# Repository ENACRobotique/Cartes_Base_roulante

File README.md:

# Carte_Base_roulante_2024
Carte custom pour une base roulante holonome basé sur la STM32G484Retx
Conçue pour d'elle même faire de l'odométrie par encodeur et gyroscope.
Le debug nécéssite une sonde externe.

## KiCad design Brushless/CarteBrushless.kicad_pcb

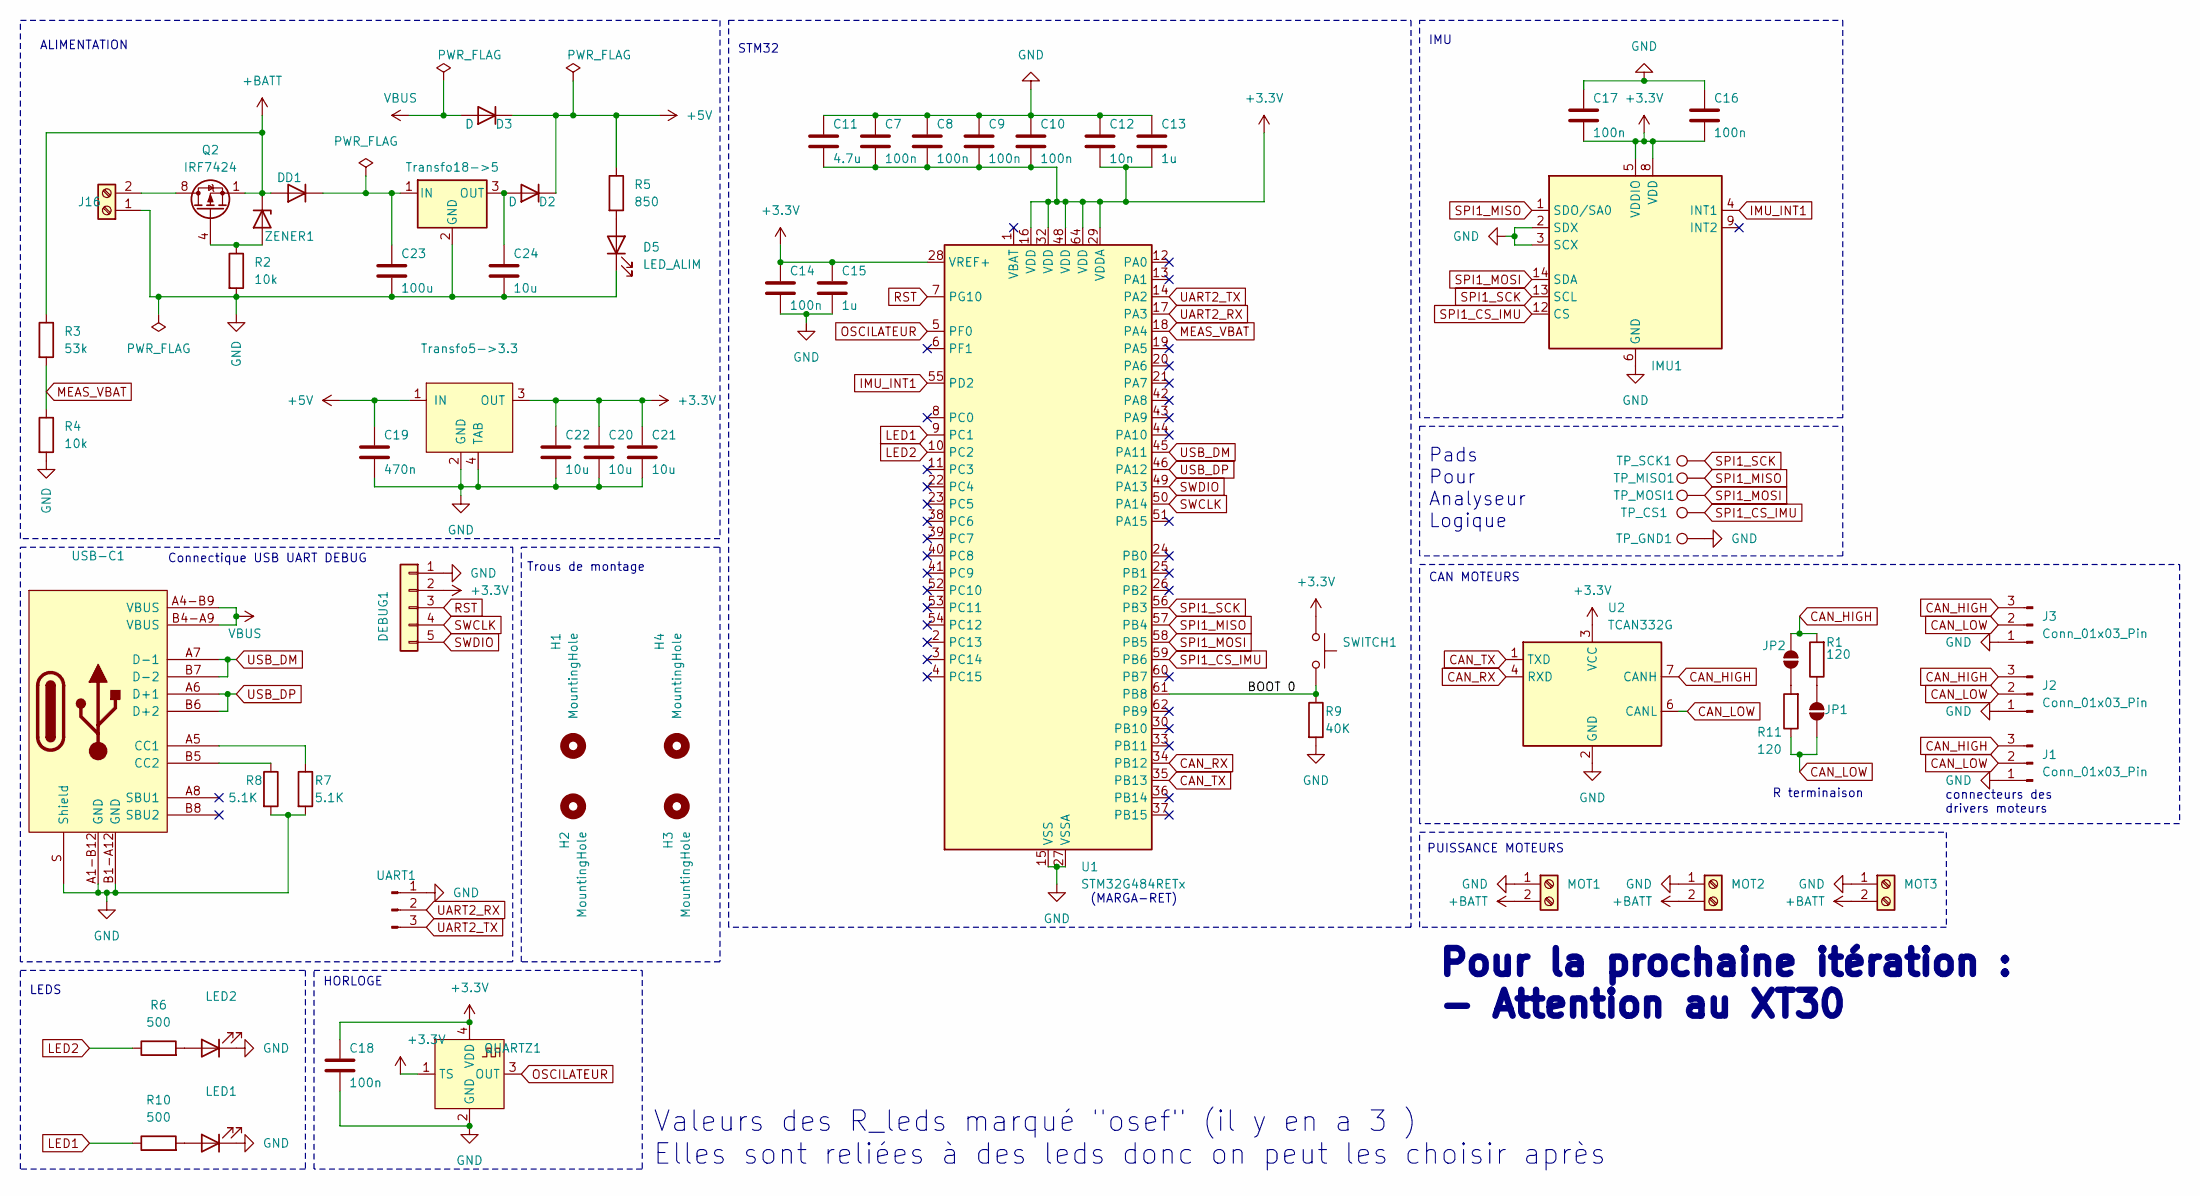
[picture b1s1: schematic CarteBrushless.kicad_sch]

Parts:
C7, C8, C9, C10, C14, C16, C17, C18: 100n; C_0603_1608Metric
C11: 4.7u; C_0603_1608Metric
C12: 10n; C_0603_1608Metric
C13, C15: 1u; C_0603_1608Metric
C19: 470n; C_0603_1608Metric
C20, C21, C22, C24: 10u; C_0603_1608Metric
C23: 100u; CP_EIA-7343-31_Kemet-D_Pad2.25x2.55mm_HandSolder
D1, D2, D3: D; Nexperia_CFP3_SOD-123W
D5: LED_ALIM; LED_0603_1608Metric
DEBUG1: DEBUG; Molex_PicoBlade_53398-0571_1x05-1MP_P1.25mm_Vertical
H1, H2, H3, H4: MountingHole; MountingHole_3.2mm_M3
IMU1: LSM6DSL; LGA-14_3x2.5mm_P0.5mm_LayoutBorder3x4y
J1, J2, J3: Conn_01x03_Pin; Molex_PicoBlade_53398-0371_1x03-1MP_P1.25mm_Vertical
J16: ALIM; TerminalBlock_bornier-2_P5.08mm
JP1, JP2: SolderJumper_2_Open; SolderJumper-2_P1.3mm_Open_RoundedPad1.0x1.5mm
LED1: LED1; LED_0603_1608Metric_Pad1.05x0.95mm_HandSolder
LED2: LED2; LED_0603_1608Metric_Pad1.05x0.95mm_HandSolder
MOT1, MOT2, MOT3: MOT3; AMASS_XT30UPB-F_1x02_P5.0mm_Vertical
Q2: IRF7424; SOIC-8_3.9x4.9mm_P1.27mm
QUARTZ1: ASCO; Osc_ASCO
R1, R11: 120; R_0805_2012Metric
R2, R4: 10k; R_0805_2012Metric
R3: 53k; R_0805_2012Metric
R5: 850; R_0805_2012Metric
R6, R10: 500; R_0805_2012Metric
R7, R8: 5.1K; R_0603_1608Metric
R9: 40K; R_0805_2012Metric
SWITCH1: SW_Push; SWITCH_DTSM31NV
TP_CS1: TestPoint; TestPoint_Pad_D1.5mm
TP_GND1: TestPoint; TestPoint_Pad_D1.5mm
TP_MISO1: TestPoint; TestPoint_Pad_D1.5mm
TP_MOSI1: TestPoint; TestPoint_Pad_D1.5mm
TP_SCK1: TestPoint; TestPoint_Pad_D1.5mm
Transfo5->3.3: LM3940IMP-3.3; LM3940IMP
Transfo18->5: R-78E5.0-1.0; Converter_DCDC_RECOM_R-78E-0.5_THT
U1: STM32G484RETx; LQFP-64_10x10mm_P0.5mm
U2: TCAN332G; SOT-23-8
UART1: Conn_01x03_Pin; Molex_PicoBlade_53398-0371_1x03-1MP_P1.25mm_Vertical
USB-C1: USB-C_12pin; USB-C_HRO_C-31-M-12
ZENER1: D_Zener; D_SOD-523

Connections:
+3.3V: C7.2, C8.2, C9.2, C10.2, C11.2, C12.2, C13.2, C14.1, C15.1, C16.2, C17.2, C18.1, C20.1, C21.1, C22.1, DEBUG1.2, IMU1.5 (VDDIO), IMU1.8 (VDD), QUARTZ1.1 (TS), QUARTZ1.4 (VDD), SWITCH1.1, Transfo5->3.3.3 (OUT), U1.16 (VDD), U1.28 (VREF+), U1.29 (VDDA), U1.32 (VDD), U1.48 (VDD), U1.64 (VDD), U2.3 (VCC)
+5V: C19.1, D2.1 (K), D3.1 (K), R5.1, Transfo5->3.3.1 (IN)
+BATT: D1.2 (A), MOT1.2, MOT2.2, MOT3.2, Q2.1 (S), Q2.2 (S), Q2.3 (S), R3.1, ZENER1.1 (K)
/BOOT 0: R9.1, SWITCH1.2, U1.61 (PB8)
CAN_HIGH: J1.3, J2.3, J3.3, JP2.2 (B), R1.2, U2.7 (CANH)
CAN_LOW: J1.2, J2.2, J3.2, JP1.1 (A), R11.1, U2.6 (CANL)
CAN_RX: U1.34 (PB12), U2.4 (RXD)
CAN_TX: U1.35 (PB13), U2.1 (TXD)
GND: C7.1, C8.1, C9.1, C10.1, C11.1, C12.1, C13.1, C14.2, C15.2, C16.1, C17.1, C18.2, C19.2, C20.2, C21.2, C22.2, C23.2, C24.2, D5.1 (K), DEBUG1.1, IMU1.2 (SDX), IMU1.3 (SCX), IMU1.6 (GND), IMU1.7 (GND), J1.1, J2.1, J3.1, LED1.1 (K), LED2.1 (K), MOT1.1, MOT2.1, MOT3.1, QUARTZ1.2 (GND), R2.2, R4.2, R7.2, R8.2, R9.2, TP_GND1.1, Transfo5->3.3.2 (GND), Transfo5->3.3.4 (TAB), Transfo18->5.2 (GND), U1.15 (VSS), U1.27 (VSSA), U1.31 (VSS), U1.47 (VSS), U1.63 (VSS), U2.2 (GND), UART1.1, USB-C1.A1-B12 (GND), USB-C1.B1-A12 (GND), USB-C1.S (Shield); also elsewhere on the board
IMU_INT1: IMU1.4 (INT1), U1.55 (PD2)
LED1: R10.1, U1.9 (PC1)
LED2: R6.1, U1.10 (PC2)
MEAS_VBAT: R3.2, R4.1, U1.18 (PA4)
unnamed 13: Q2.5 (D), Q2.6 (D), Q2.7 (D), Q2.8 (D); also elsewhere on the board
unnamed: C23.1, D1.1 (K), Transfo18->5.1 (IN)
unnamed: C24.1, D2.2 (A), Transfo18->5.3 (OUT)
unnamed: D5.2 (A), R5.2
unnamed: JP1.2 (B), R1.1
unnamed: JP2.1 (A), R11.2
unnamed: LED1.2 (A), R10.2
unnamed: LED2.2 (A), R6.2
unnamed: Q2.4 (G), R2.1, ZENER1.2 (A)
unnamed: R7.1, USB-C1.A5 (CC1)
unnamed: R8.1, USB-C1.B5 (CC2)
OSCILATEUR: QUARTZ1.3 (OUT), U1.5 (PF0)
RST: DEBUG1.3, U1.7 (PG10)
SPI1_CS_IMU: IMU1.12 (CS), TP_CS1.1, U1.59 (PB6)
SPI1_MISO: IMU1.1 (SDO/SA0), TP_MISO1.1, U1.57 (PB4)
SPI1_MOSI: IMU1.14 (SDA), TP_MOSI1.1, U1.58 (PB5)
SPI1_SCK: IMU1.13 (SCL), TP_SCK1.1, U1.56 (PB3)
SWCLK: DEBUG1.4, U1.50 (PA14)
SWDIO: DEBUG1.5, U1.49 (PA13)
UART2_RX: U1.17 (PA3), UART1.2
UART2_TX: U1.14 (PA2), UART1.3
USB_DM: U1.45 (PA11), USB-C1.A7 (D-1), USB-C1.B7 (D-2)
USB_DP: U1.46 (PA12), USB-C1.A6 (D+1), USB-C1.B6 (D+2)
VBUS: D3.2 (A), USB-C1.A4-B9 (VBUS), USB-C1.B4-A9 (VBUS)

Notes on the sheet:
Valeurs des R_leds marqué "osef" (il y en a 3 ) Elles sont reliées à des leds donc on peut les choisir après
IMU
LEDS
Trous de montage
connecteurs des drivers moteurs
CAN MOTEURS
HORLOGE
Pour la prochaine itération : - Attention au XT30
(MARGA-RET)
Pads Pour Analyseur Logique
PUISSANCE MOTEURS
STM32
ALIMENTATION
R terminaison
Connectique USB UART DEBUG

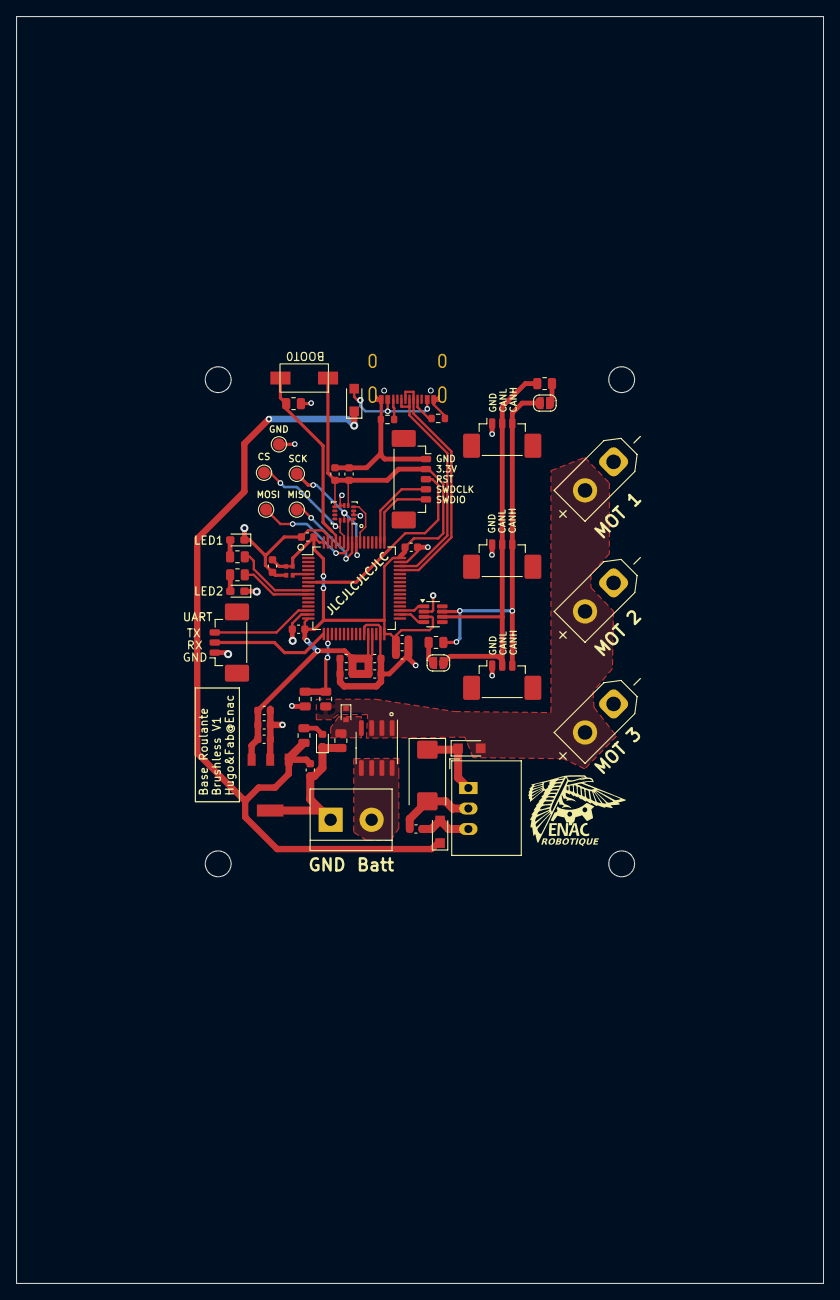
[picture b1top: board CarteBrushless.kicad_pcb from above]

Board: 2 copper layers, 100.0 x 157.0 mm, 65 parts (0 on the bottom side), 37 nets.

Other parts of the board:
ALIM1: ALIM; TerminalBlock_bornier-2_P5.08mm

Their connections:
GND: ALIM1.1; also elsewhere on the board
unnamed 13: ALIM1.2; also elsewhere on the board

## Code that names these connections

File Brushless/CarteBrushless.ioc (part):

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Mcu.Name=STM32G484RETx
Mcu.Package=LQFP64
Mcu.UserName=STM32G484RETx
PA11.Mode=Device
PA11.Signal=USB_DM
PA12.Mode=Device
PA12.Signal=USB_DP
PA13.Mode=Serial_Wire
PA13.Signal=SYS_JTMS-SWDIO
PA14.Mode=Serial_Wire
PA14.Signal=SYS_JTCK-SWCLK
PA2.Mode=Asynchronous
PA2.Signal=USART2_TX
PA3.Mode=Asynchronous
PA3.Signal=USART2_RX
PA4.Mode=IN17-Single-Ended
PA4.Signal=ADC2_IN17
PB12.Mode=FDCAN_Activate
PB12.Signal=FDCAN2_RX
PB13.Mode=FDCAN_Activate
PB13.Signal=FDCAN2_TX
PB3.Mode=Full_Duplex_Master
PB3.Signal=SPI1_SCK
PB4.Mode=Full_Duplex_Master
PB4.Signal=SPI1_MISO
PB5.Mode=Full_Duplex_Master
PB5.Signal=SPI1_MOSI
PB6.GPIOParameters=GPIO_Label
PB6.GPIO_Label=SPI1_CS_IMU
PB6.Signal=GPIO_Output
PB8-BOOT0.GPIOParameters=GPIO_Label
PB8-BOOT0.GPIO_Label=BOOT0
PB8-BOOT0.Signal=GPIO_Input
PC1.GPIOParameters=GPIO_Label
PC1.GPIO_Label=LED1
PC1.Signal=GPIO_Output
PC10.Mode=Asynchronous
PC10.Signal=UART4_TX
PC11.Mode=Asynchronous
PC11.Signal=UART4_RX
PC2.GPIOParameters=GPIO_Label
PC2.GPIO_Label=LED2
PC2.Signal=GPIO_Output
PD2.GPIOParameters=GPIO_Label
PD2.GPIO_Label=IMU_INT1
PD2.Signal=GPIO_Input
PF0-OSC_IN.Mode=HSE-External-Clock-Source
PF0-OSC_IN.Signal=RCC_OSC_IN
PG10-NRST.GPIOParameters=GPIO_Label
PG10-NRST.GPIO_Label=RST
PG10-NRST.Signal=GPIO_Input
RCC.HSE_VALUE=8000000
RCC.SYSCLKFreq_VALUE=16000000
board=custom

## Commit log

2023-11-22 add capacitors
2023-11-23 IMU + SPI
2023-11-23 usb + protection + cristal + leds + adc
2023-11-23 cubemx stm
2023-11-23 add testpoints for SPI
2023-11-24 ajout empreintes wip
2023-11-25 placement préliminaire
2023-11-26 compact : alim, encodeur, imu
2023-11-30 placement amélioré
2023-11-30 j'essaie
2023-11-30 changement alim et plan BATT
2023-12-01 + batt ok ?
2023-12-01 routage avançé
2023-12-01 manque plan GNA et pads
2023-12-01 almost ended , need GND
2023-12-02 Routage Terminé git status !
2023-12-02 j'ai pas fait Ctrl S ...
2023-12-02 Marquage
2023-12-04 Carte terminé git status!
2023-12-05 ajuste espacement trous
2023-12-05 corrections + courbe + stencil
2023-12-05 correctif
2023-12-07 fix DRC
2024-02-02 production attention stencil trop grand de quelques mm
2024-12-19 rangement du repo
2024-12-19 Schematic Brushless
2024-12-19 tentative de fix du bug de reset
2024-12-19 placement PCB
2024-12-20 Routage fini
2024-12-20 Pad BATT+ Solides
2025-01-23 change SWD footprint
2025-01-23 Reduce mounting holes spacing
2025-01-23 Ajustement des trous
2025-01-23 UART
2025-01-23 Gerber et stencil
2025-01-23 remove stencil
2025-01-23 le bon stencil cette fois
2025-01-23 on vire ça
2025-01-24 save stencil
2025-02-06 liste des composants
2025-02-11 composants
2025-02-13 resistance LED + schema soudure
